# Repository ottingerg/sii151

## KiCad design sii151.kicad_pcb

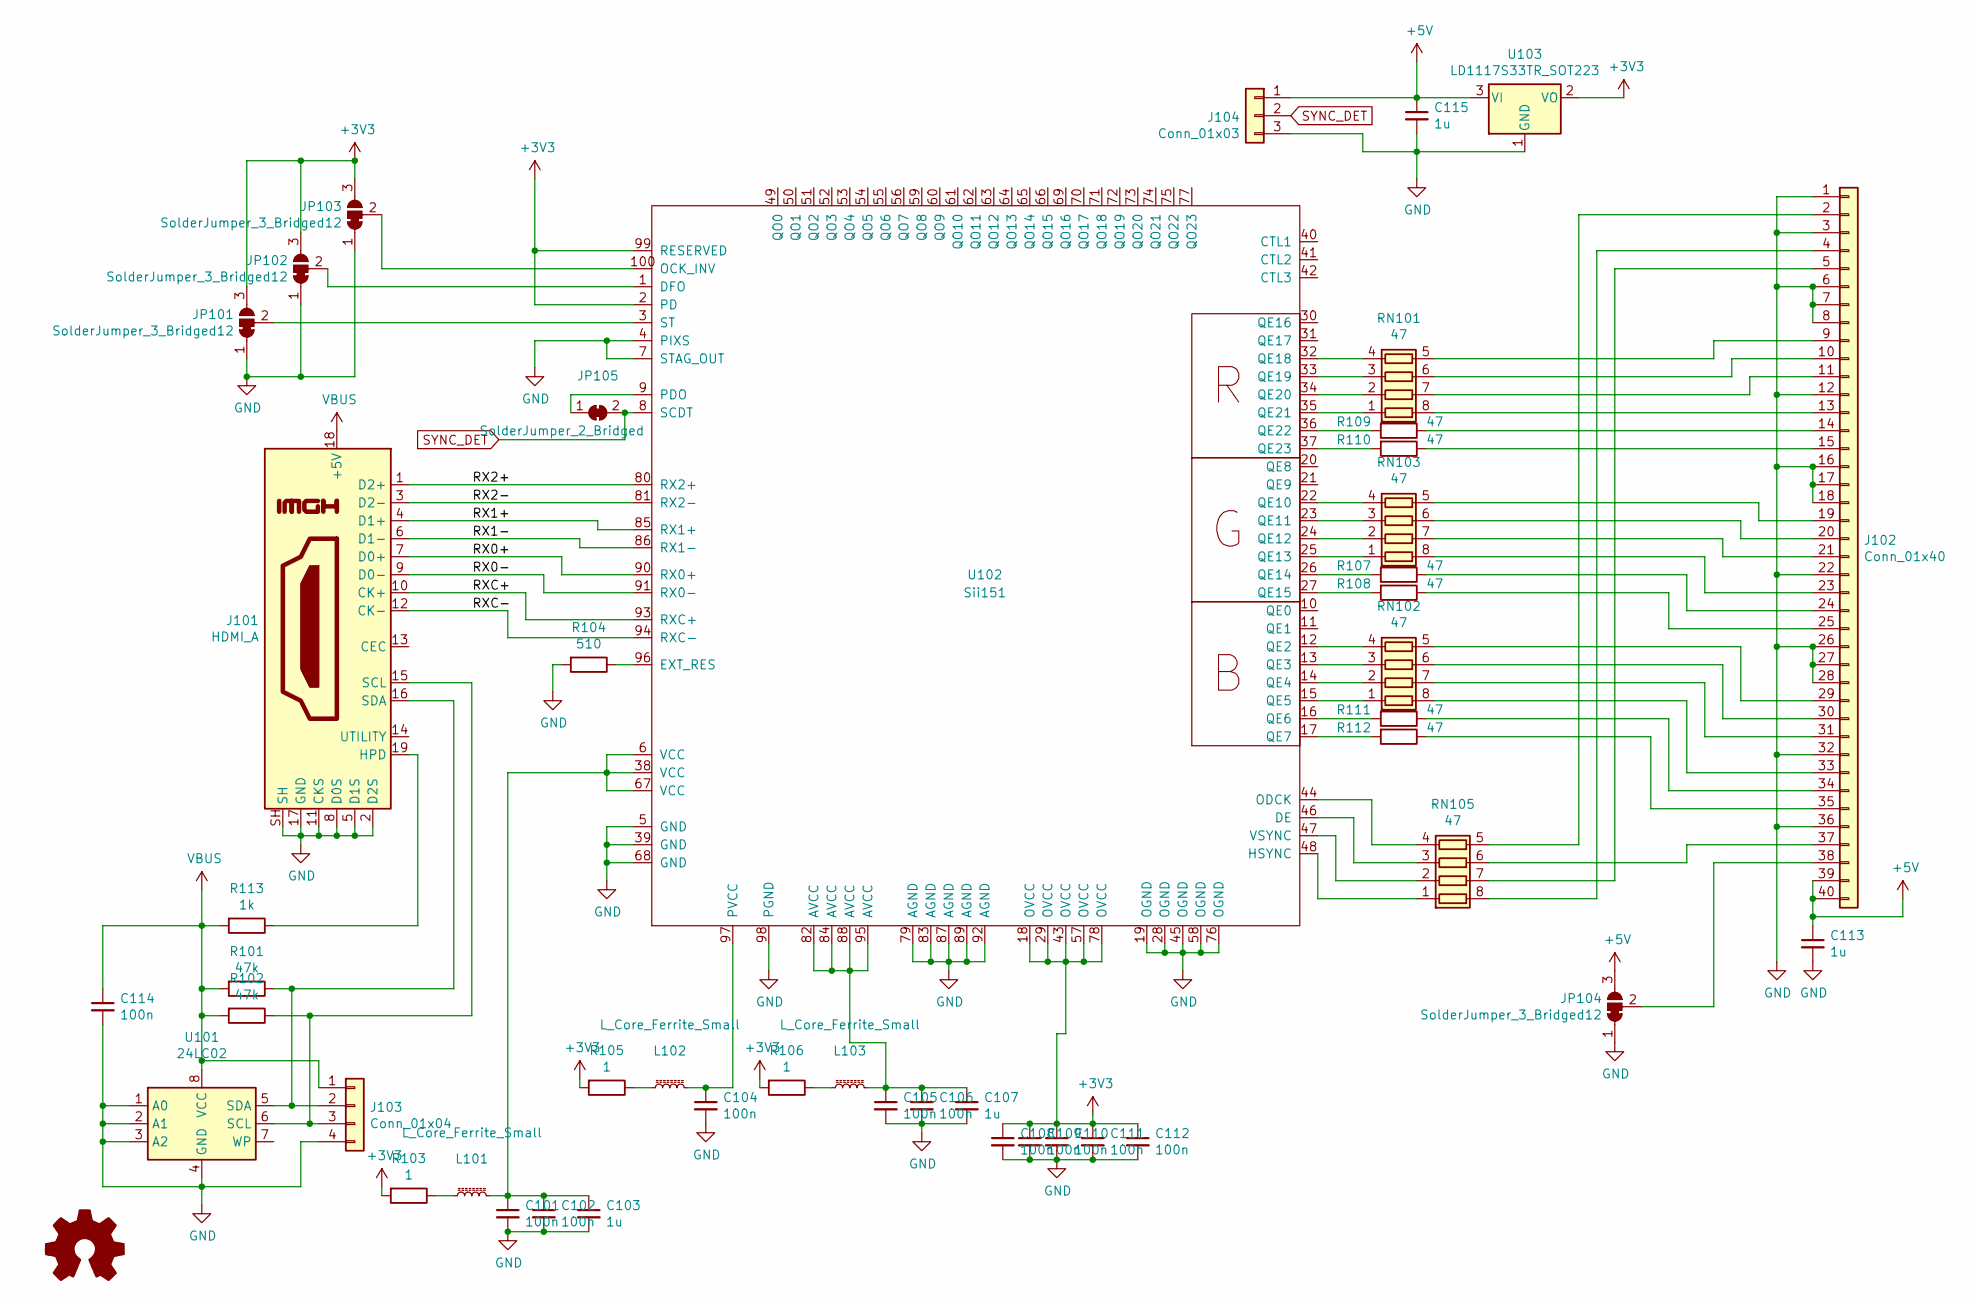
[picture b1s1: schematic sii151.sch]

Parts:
C101, C102, C104, C105, C106, C108, C109, C110, C111, C112, C114: 100n; C_0402_1005Metric
C103, C107, C113, C115: 1u; C_0603_1608Metric
J101: HDMI_A; wuerth_685119134923
J102: Conn_01x40; TE_4-1734839-0_1x40-1MP_P0.5mm_Horizontal
J103: Conn_01x04; PinHeader_1x04_P2.00mm_Vertical
J104: Conn_01x03; PinHeader_1x03_P2.54mm_Vertical
JP101, JP102, JP103, JP104: SolderJumper_3_Bridged12; SolderJumper-3_P1.3mm_Bridged12_RoundedPad1.0x1.5mm_NumberL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
JP105: SolderJumper_2_Bridged; SolderJumper-2_P1.3mm_Bridged_RoundedPad1.0x1.5mm
L101, L102, L103: L_Core_Ferrite_Small; L_0805_2012Metric
R101, R102: 47k; R_0402_1005Metric
R103, R105, R106: 1; R_0402_1005Metric
R104: 510; R_0402_1005Metric
R107, R108, R109, R110, R111, R112: 47; R_0402_1005Metric
R113: 1k; R_0402_1005Metric
RN101, RN102, RN103, RN105: 47; R_Array_Convex_4x0402
U101: 24LC02; SO-8_3.9x4.9mm_P1.27mm
U102: Sii151; LQFP-100_14x14mm_P0.5mm
U103: LD1117S33TR_SOT223; SOT-223-3_TabPin2

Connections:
+3V3: C108.1, C109.1, C110.1, C111.1, C112.1, JP101.3 (B), JP102.3 (B), JP103.3 (B), R103.2, R105.2, R106.2, U102.2 (PD), U102.18 (OVCC), U102.29 (OVCC), U102.43 (OVCC), U102.57 (OVCC), U102.78 (OVCC), U102.99 (RESERVED), U103.2 (VO)
+5V: C113.1, C115.1, J102.39, J102.40, J104.1, JP104.3 (B), U103.3 (VI)
/RX0+: J101.7 (D0+), U102.90 (RX0+)
/RX0-: J101.9 (D0-), U102.91 (RX0-)
/RX1+: J101.4 (D1+), U102.85 (RX1+)
/RX1-: J101.6 (D1-), U102.86 (RX1-)
/RX2+: J101.1 (D2+), U102.80 (RX2+)
/RX2-: J101.3 (D2-), U102.81 (RX2-)
/RXC+: J101.10 (CK+), U102.93 (RXC+)
/RXC-: J101.12 (CK-), U102.94 (RXC-)
GND: C101.2, C102.2, C103.2, C104.2, C105.2, C106.2, C107.2, C108.2, C109.2, C110.2, C111.2, C112.2, C113.2, C114.2, C115.2, J101.2 (D2S), J101.5 (D1S), J101.8 (D0S), J101.11 (CKS), J101.17 (GND), J101.SH, J102.1, J102.3, J102.6, J102.7, J102.8, J102.12, J102.16, J102.17, J102.18, J102.22, J102.26, J102.27, J102.28, J102.32, J102.36, J103.4, J104.3, JP101.1 (A), JP102.1 (A), JP103.1 (A), JP104.1 (A), R104.2, U101.1 (A0), U101.2 (A1), U101.3 (A2), U101.4 (GND), U102.4 (PIXS), U102.5 (GND), U102.7 (STAG_OUT), U102.19 (OGND), U102.28 (OGND), U102.39 (GND), U102.45 (OGND), U102.58 (OGND), U102.68 (GND), U102.76 (OGND), U102.79 (AGND), U102.83 (AGND), U102.87 (AGND), U102.89 (AGND), U102.92 (AGND), U102.98 (PGND), U103.1 (GND)
unnamed: C101.1, C102.1, C103.1, L101.2, U102.6 (VCC), U102.38 (VCC), U102.67 (VCC)
unnamed: C104.1, L102.2, U102.97 (PVCC)
unnamed: C105.1, C106.1, C107.1, L103.2, U102.82 (AVCC), U102.84 (AVCC), U102.88 (AVCC), U102.95 (AVCC)
unnamed: J101.15 (SCL), J103.3, R102.1, U101.6 (SCL)
unnamed: J101.16 (SDA), J103.2, R101.1, U101.5 (SDA)
unnamed: J101.19 (HPD), R113.1
unnamed: J102.2, RN105.5 (R4.2)
unnamed: J102.4, RN105.8 (R1.2)
unnamed: J102.5, RN105.7 (R2.2)
unnamed: J102.9, RN101.5 (R4.2)
unnamed: J102.10, RN101.6 (R3.2)
unnamed: J102.11, RN101.7 (R2.2)
unnamed: J102.13, RN101.8 (R1.2)
unnamed: J102.14, R109.1
unnamed: J102.15, R110.1
unnamed: J102.19, RN103.5 (R4.2)
unnamed: J102.20, RN103.6 (R3.2)
unnamed: J102.21, RN103.7 (R2.2)
unnamed: J102.23, RN103.8 (R1.2)
unnamed: J102.24, R107.1
unnamed: J102.25, R108.1
unnamed: J102.29, RN102.5 (R4.2)
unnamed: J102.30, RN102.6 (R3.2)
unnamed: J102.31, RN102.7 (R2.2)
unnamed: J102.33, RN102.8 (R1.2)
unnamed: J102.34, R111.1
unnamed: J102.35, R112.1
unnamed: J102.37, RN105.6 (R3.2)
unnamed: J102.38, JP104.2 (C)
unnamed: JP101.2 (C), U102.3 (ST)
unnamed: JP102.2 (C), U102.1 (DFO)
unnamed: JP103.2 (C), U102.100 (OCK_INV)
unnamed: JP105.1 (A), U102.9 (PDO)
unnamed: L101.1, R103.1
unnamed: L102.1, R105.1
unnamed: L103.1, R106.1
unnamed: R104.1, U102.96 (EXT_RES)
unnamed: R107.2, U102.26 (QE14)
unnamed: R108.2, U102.27 (QE15)
unnamed: R109.2, U102.36 (QE22)
unnamed: R110.2, U102.37 (QE23)
unnamed: R111.2, U102.16 (QE6)
unnamed: R112.2, U102.17 (QE7)
unnamed: RN101.1 (R1.1), U102.35 (QE21)
unnamed: RN101.2 (R2.1), U102.34 (QE20)
unnamed: RN101.3 (R3.1), U102.33 (QE19)
unnamed: RN101.4 (R4.1), U102.32 (QE18)
unnamed: RN102.1 (R1.1), U102.15 (QE5)
unnamed: RN102.2 (R2.1), U102.14 (QE4)
unnamed: RN102.3 (R3.1), U102.13 (QE3)
unnamed: RN102.4 (R4.1), U102.12 (QE2)
unnamed: RN103.1 (R1.1), U102.25 (QE13)
unnamed: RN103.2 (R2.1), U102.24 (QE12)
unnamed: RN103.3 (R3.1), U102.23 (QE11)
unnamed: RN103.4 (R4.1), U102.22 (QE10)
unnamed: RN105.1 (R1.1), U102.48 (HSYNC)
unnamed: RN105.2 (R2.1), U102.47 (VSYNC)
unnamed: RN105.3 (R3.1), U102.46 (DE)
unnamed: RN105.4 (R4.1), U102.44 (ODCK)
SYNC_DET: J104.2, JP105.2 (B), U102.8 (SCDT)
VBUS: C114.1, J101.18 (+5V), J103.1, R101.2, R102.2, R113.2, U101.8 (VCC)

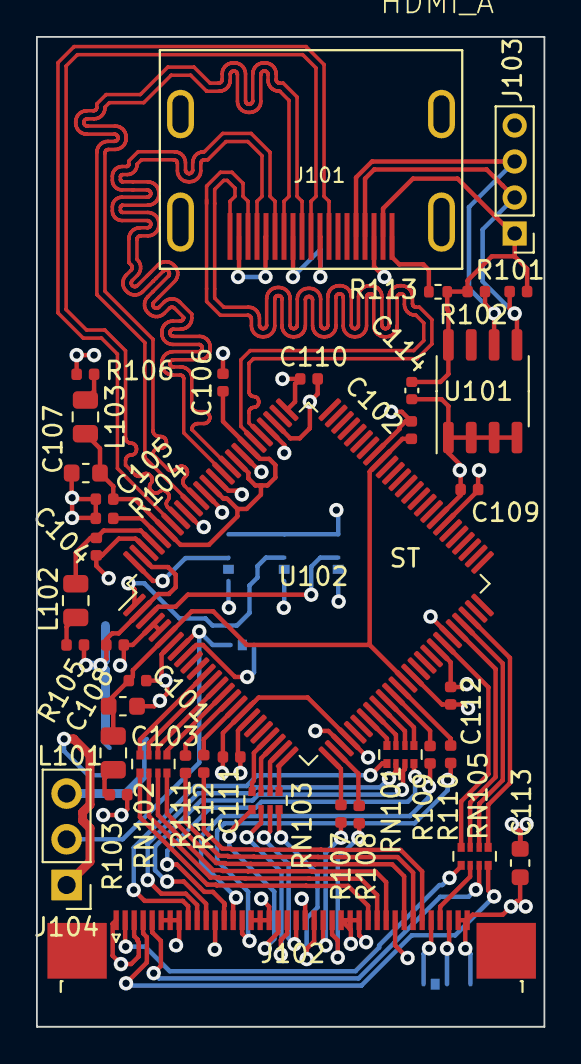
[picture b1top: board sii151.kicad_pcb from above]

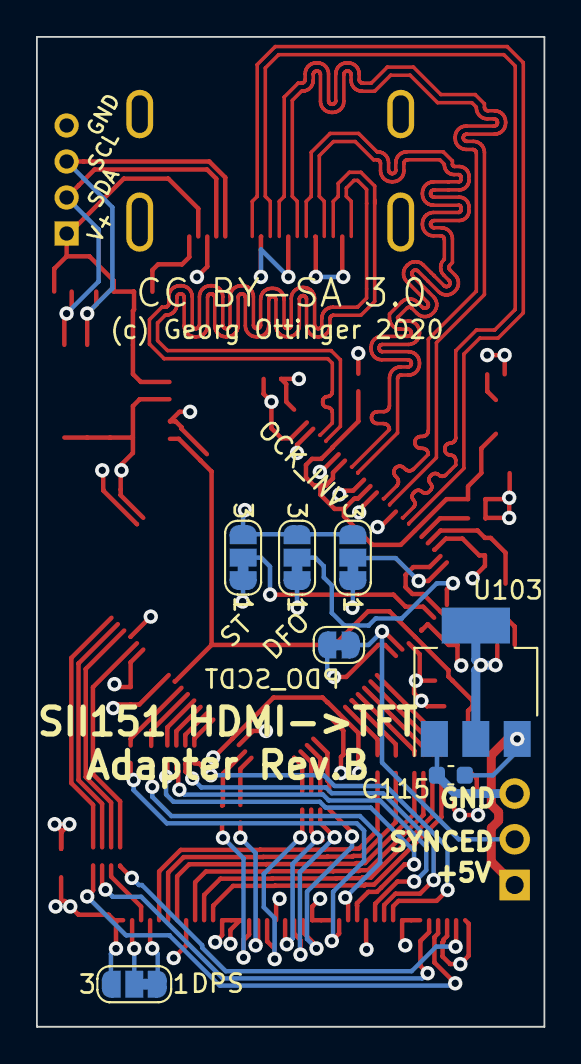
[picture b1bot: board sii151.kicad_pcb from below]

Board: 4 copper layers, 28.2 x 55.0 mm, 47 parts (7 on the bottom side), 72 nets.

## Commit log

2020-09-20 initial
2020-09-22 Rev.A ordered
2020-09-22 Rev.A
2020-09-22 added missing fpc lib
2020-10-07 added edid.dat
2020-10-11 Rev.B

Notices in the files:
sii151.kicad_pcb:
CC BY-SA 3.0
